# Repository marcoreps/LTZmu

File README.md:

# LTZmu

## -- Work in progress --

The goal of this project is to create a low cost 10V voltage transfer standard for calibrating precision measurement devices (e.g. Fluke 732A). The project is based around the <a href="https://www.analog.com/en/products/ltz1000.html">LTZ1000</a> by analog devices

For further information click <a href="https://youtu.be/N1F4duEZR_s?t=871">here</a> or visit the YouTube and search for the Video "Fluke 732A DC Voltage Standard & low cost DIY attempt" (Information about the LTZmu starts at 14:31)

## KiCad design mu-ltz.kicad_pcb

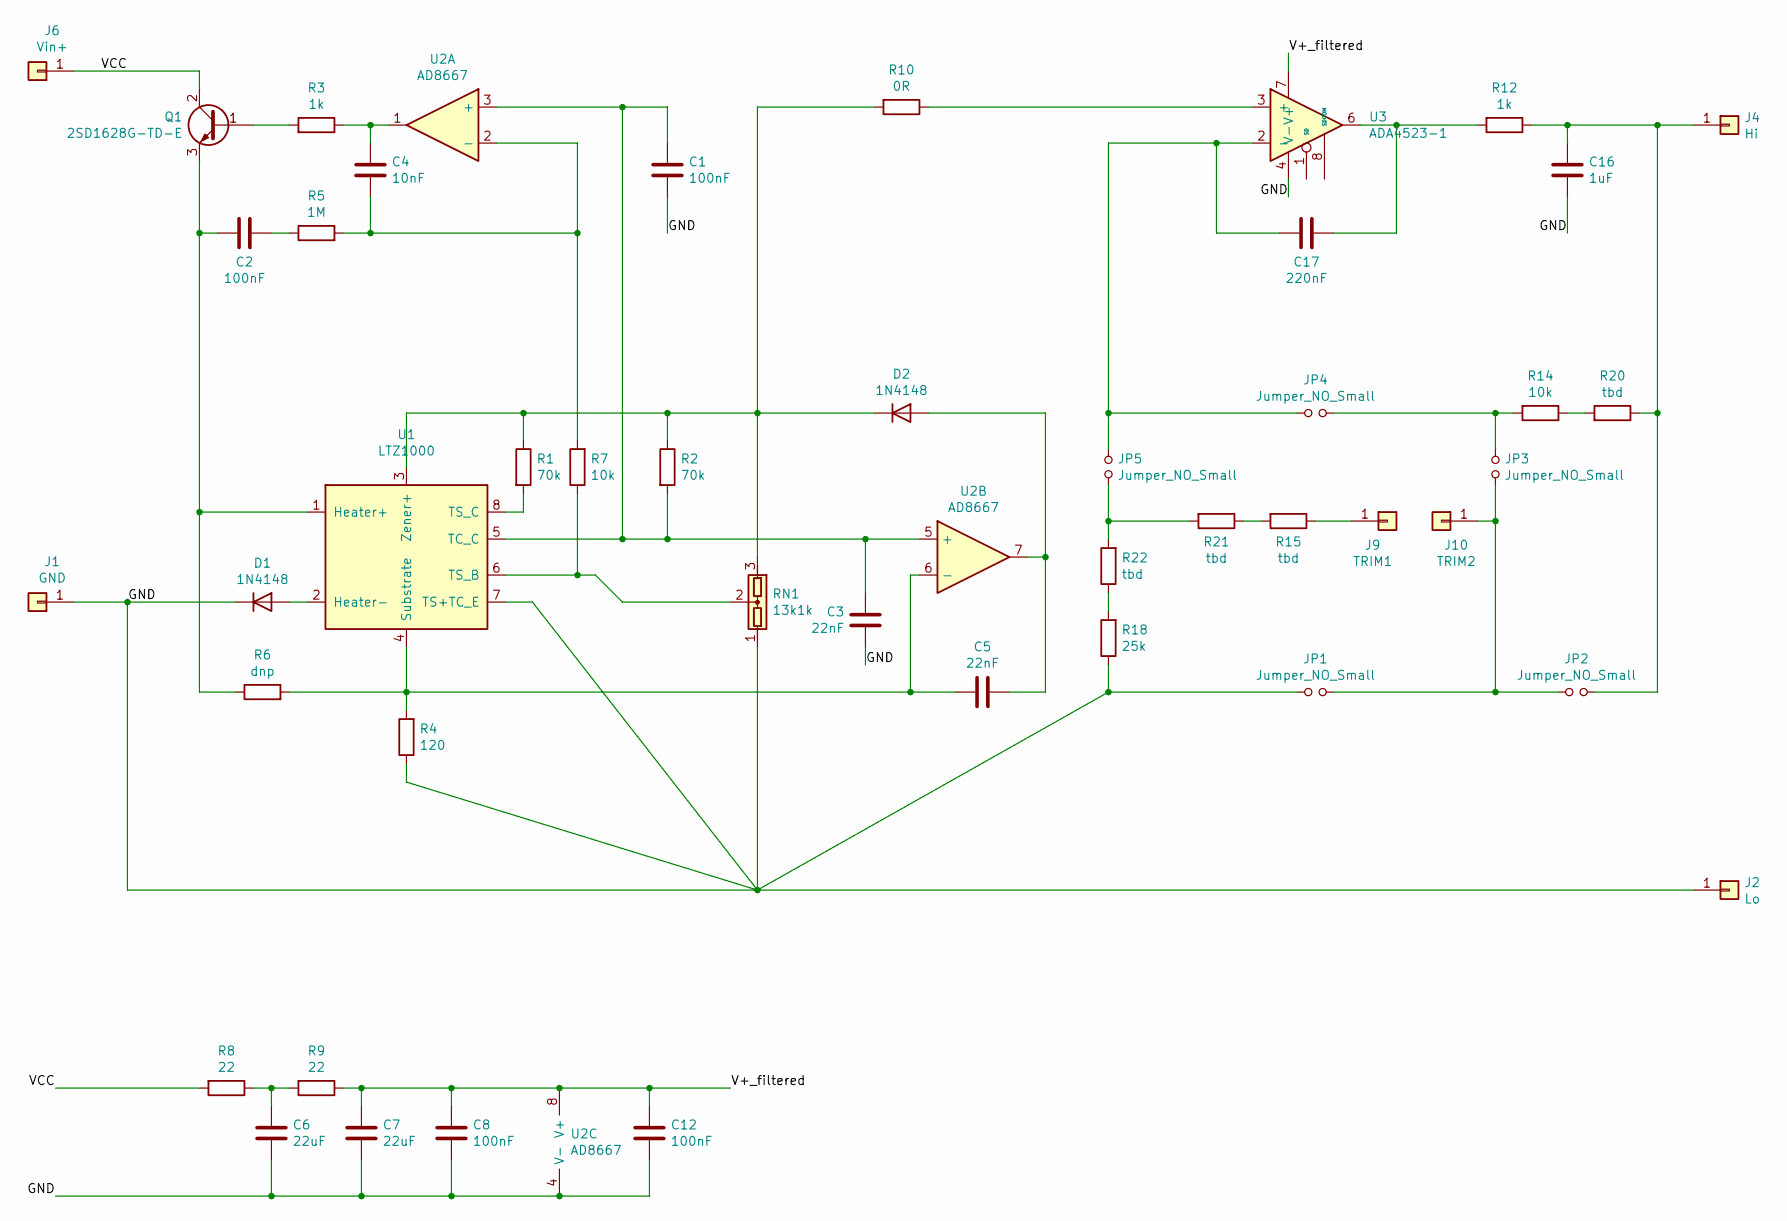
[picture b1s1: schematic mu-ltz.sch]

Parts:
C1, C2, C8, C12: 100nF; C_0603_1608Metric
C3, C5: 22nF; C_0603_1608Metric
C4: 10nF; C_0603_1608Metric
C6, C7: 22uF; C_0805_2012Metric
C16: 1uF; C_0603_1608Metric
C17: 220nF; C_0603_1608Metric
D1, D2: 1N4148; D_SOD-323
J1: GND; SolderWirePad_1x01_Drill1mm
J2: Lo; SolderWirePad_1x01_Drill1mm
J4: Hi; SolderWirePad_1x01_Drill1mm
J6: Vin+; SolderWirePad_1x01_Drill1mm
J9: TRIM1; SolderWirePad_1x01_Drill1mm
J10: TRIM2; SolderWirePad_1x01_Drill1mm
JP1, JP2, JP3, JP4, JP5: Jumper_NO_Small; SolderJumper-2_P1.3mm_Open_RoundedPad1.0x1.5mm
Q1: 2SD1628G-TD-E; SOT-89-3
R1, R2: 70k; R_0805_2012Metric
R3, R12: 1k; R_0603_1608Metric
R4: 120; R_0805_2012Metric
R5: 1M; R_0603_1608Metric
R6: dnp; R_0603_1608Metric
R7: 10k; R_0603_1608Metric
R8, R9: 22; R_0805_2012Metric
R10: 0R; R_0603_1608Metric
R14: 10k; R_1206_3216Metric
R15, R20, R21, R22: tbd; R_1206_3216Metric
R18: 25k; R_1206_3216Metric
RN1: 13k1k; SIP-3
U1: LTZ1000; TO-5-8
U2: AD8667; MSOP-8_3x3mm_P0.65mm
U3: ADA4523-1; MSOP-8_3x3mm_P0.65mm

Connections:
/GND: C1.1, C3.1, C6.1, C7.1, C8.1, C12.1, C16.2, D1.1 (K), J1.1, J2.1, JP1.1, R4.1, R18.1, RN1.1, U1.7 (TS+TC_E), U2.4 (V-), U3.4 (V-)
/V+_filtered: C7.2, C8.2, C12.2, R9.1, U2.8 (V+), U3.7 (V+)
/VCC: J6.1, Q1.2 (C), R8.2
unnamed: C1.2, C3.2, R2.2, U1.5 (TC_C), U2.3 (+), U2.5 (+)
unnamed: C2.1, R5.1
unnamed: C2.2, Q1.3 (E), R6.1, U1.1 (Heater+)
unnamed: C4.1, R5.2, R7.2, U2.2 (-)
unnamed: C4.2, R3.1, U2.1
unnamed: C5.1, R4.2, R6.2, U1.4 (Substrate), U2.6 (-)
unnamed: C5.2, D2.2 (A), U2.7
unnamed: C6.2, R8.1, R9.2
unnamed: C16.1, J4.1, JP2.2, R12.1, R20.1
unnamed: C17.1, JP4.1, JP5.1, U3.2 (-)
unnamed: C17.2, R12.2, U3.6
unnamed: D1.2 (A), U1.2 (Heater-)
unnamed: D2.1 (K), R1.1, R2.1, R10.2, RN1.3, U1.3 (Zener+)
unnamed: J9.1, R15.1
unnamed: J10.1, JP1.2, JP2.1, JP3.1
unnamed: JP3.2, JP4.2, R14.2
unnamed: JP5.2, R21.2, R22.2
unnamed: Q1.1 (B), R3.2
unnamed: R1.2, U1.8 (TS_C)
unnamed: R7.1, RN1.2, U1.6 (TS_B)
unnamed: R10.1, U3.3 (+)
unnamed: R14.1, R20.2
unnamed: R15.2, R21.1
unnamed: R18.2, R22.1

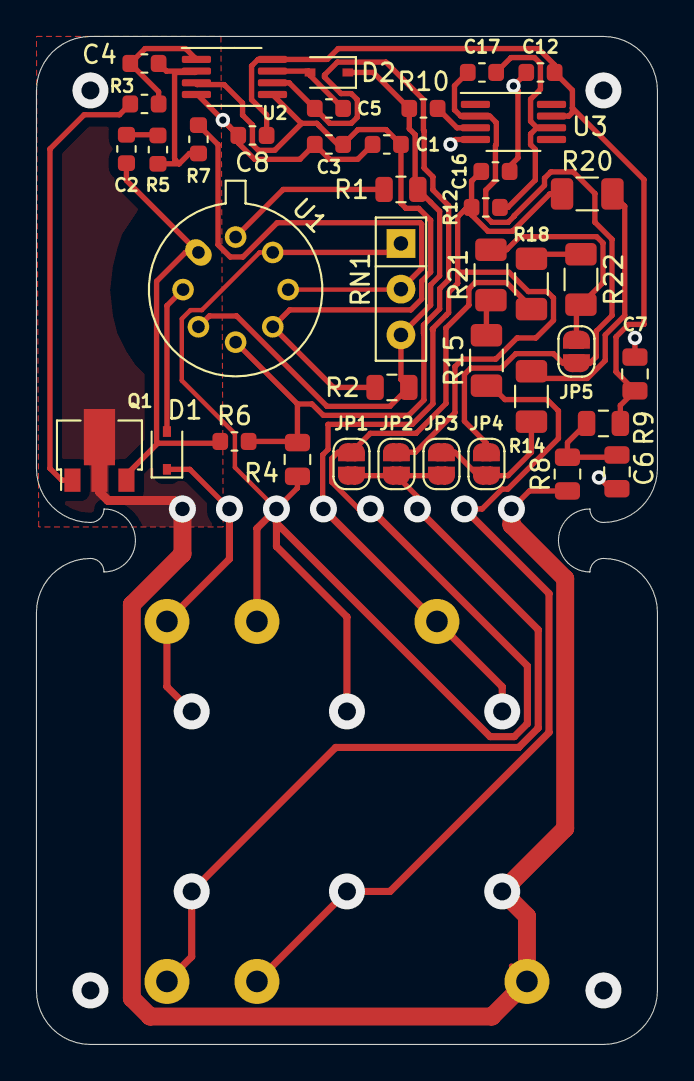
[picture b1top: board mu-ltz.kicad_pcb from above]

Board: 2 copper layers, 34.5 x 56.0 mm, 46 parts (0 on the bottom side), 27 nets.

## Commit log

2021-07-09 Rev. 2 started
2021-07-30 Rev. 0.2 layout finished, not yet tested
2021-07-30 46161
2022-08-06 Update README.md
    Ive added your youtube video in the desciption as well as made full sentences out of your provided informations provided on the video and previous readme
